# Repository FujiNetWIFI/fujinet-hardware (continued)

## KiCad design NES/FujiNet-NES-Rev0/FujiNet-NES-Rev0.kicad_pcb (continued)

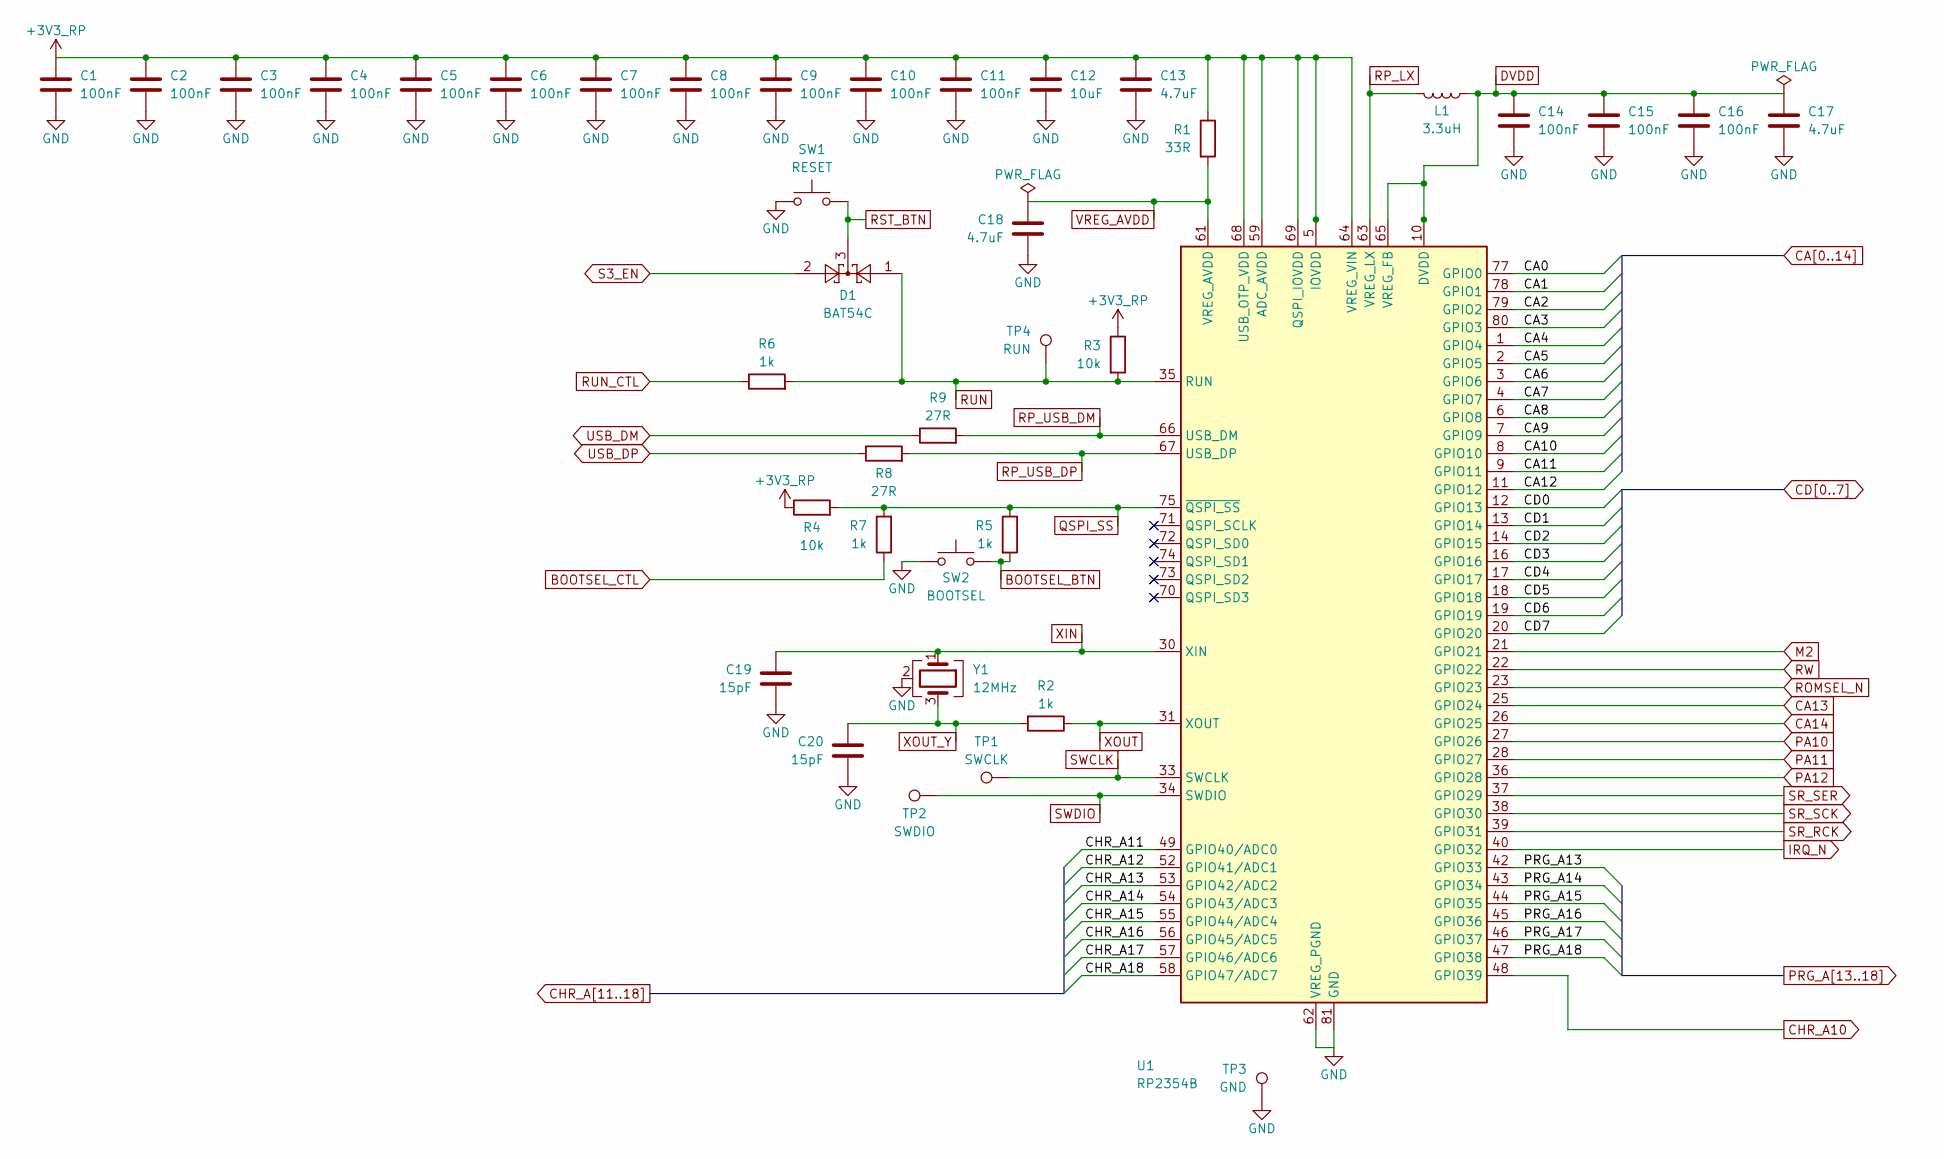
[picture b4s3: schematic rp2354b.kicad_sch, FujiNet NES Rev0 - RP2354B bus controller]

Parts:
C1, C2, C3, C4, C5, C6, C7, C8, C9, C10, C11, C14, C15, C16: 100nF; C_0603_1608Metric; MPN CC0603KRX7R9BB104; LCSC C14663
C12: 10uF; C_0603_1608Metric; MPN CL10A106KP8NNNC; LCSC C19702
C13, C17, C18: 4.7uF; C_0603_1608Metric; MPN CL10A475KO8NNNC; LCSC C19666
C19, C20: 15pF; C_0603_1608Metric; MPN CL10C150JB8NNNC; LCSC C1644
D1: BAT54C; SOT-23; MPN BAT54C,215; LCSC C37704
L1: 3.3uH; RPI_L_AOTA-B201610S3R3; MPN AOTA-B201610S3R3-101-T; LCSC C42411119
R1: 33R; R_0603_1608Metric; MPN 0603WAF330JT5E; LCSC C23140
R2, R5, R6, R7: 1k; R_0603_1608Metric; MPN 0603WAF1001T5E; LCSC C21190
R3, R4: 10k; R_0603_1608Metric; MPN 0603WAF1002T5E; LCSC C25804
R8, R9: 27R; R_0603_1608Metric; MPN 0603WAF270JT5E; LCSC C25190
SW1: RESET; SW_SPST_TL3342; MPN TL3342F160QG; LCSC C2886898
SW2: BOOTSEL; SW_SPST_TL3342; MPN TL3342F160QG; LCSC C2886898
TP1: SWCLK; TestPoint_Pad_D1.5mm
TP2: SWDIO; TestPoint_Pad_D1.5mm
TP3: GND; TestPoint_Pad_D1.5mm
TP4: RUN; TestPoint_Pad_D1.5mm
U1: RP2354B; QFN-80-1EP_10x10mm_P0.4mm_EP3.4x3.4mm; MPN RP2354B; LCSC C39843328
Y1: 12MHz; Crystal_SMD_3225-4Pin_3.2x2.5mm; MPN ABM8-272-T3; LCSC C20625731

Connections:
+3V3_RP: C1.1, C2.1, C3.1, C4.1, C5.1, C6.1, C7.1, C8.1, C9.1, C10.1, C11.1, C12.1, C13.1, R1.1, R3.1, R4.1, U1.5 (IOVDD), U1.15 (IOVDD), U1.24 (IOVDD), U1.29 (IOVDD), U1.41 (IOVDD), U1.50 (IOVDD), U1.59 (ADC_AVDD), U1.60 (IOVDD), U1.64 (VREG_VIN), U1.68 (USB_OTP_VDD), U1.69 (QSPI_IOVDD), U1.76 (IOVDD); also elsewhere on the board
BOOTSEL_BTN: R5.2, SW2.1
BOOTSEL_CTL: R7.1; also elsewhere on the board
CA0: U1.77 (GPIO0); also elsewhere on the board
CA1: U1.78 (GPIO1); also elsewhere on the board
CA2: U1.79 (GPIO2); also elsewhere on the board
CA3: U1.80 (GPIO3); also elsewhere on the board
CA4: U1.1 (GPIO4); also elsewhere on the board
CA5: U1.2 (GPIO5); also elsewhere on the board
CA6: U1.3 (GPIO6); also elsewhere on the board
CA7: U1.4 (GPIO7); also elsewhere on the board
CA8: U1.6 (GPIO8); also elsewhere on the board
CA9: U1.7 (GPIO9); also elsewhere on the board
CA10: U1.8 (GPIO10); also elsewhere on the board
CA11: U1.9 (GPIO11); also elsewhere on the board
CA12: U1.11 (GPIO12); also elsewhere on the board
CA13: U1.25 (GPIO24); also elsewhere on the board
CA14: U1.26 (GPIO25); also elsewhere on the board
CD0: U1.12 (GPIO13); also elsewhere on the board
CD1: U1.13 (GPIO14); also elsewhere on the board
CD2: U1.14 (GPIO15); also elsewhere on the board
CD3: U1.16 (GPIO16); also elsewhere on the board
CD4: U1.17 (GPIO17); also elsewhere on the board
CD5: U1.18 (GPIO18); also elsewhere on the board
CD6: U1.19 (GPIO19); also elsewhere on the board
CD7: U1.20 (GPIO20); also elsewhere on the board
CHR_A10: U1.48 (GPIO39); also elsewhere on the board
CHR_A11: U1.49 (GPIO40/ADC0); also elsewhere on the board
CHR_A12: U1.52 (GPIO41/ADC1); also elsewhere on the board
CHR_A13: U1.53 (GPIO42/ADC2); also elsewhere on the board
CHR_A14: U1.54 (GPIO43/ADC3); also elsewhere on the board
CHR_A15: U1.55 (GPIO44/ADC4); also elsewhere on the board
CHR_A16: U1.56 (GPIO45/ADC5); also elsewhere on the board
CHR_A17: U1.57 (GPIO46/ADC6); also elsewhere on the board
CHR_A18: U1.58 (GPIO47/ADC7); also elsewhere on the board
DVDD: C14.1, C15.1, C16.1, C17.1, L1.1, U1.10 (DVDD), U1.32 (DVDD), U1.51 (DVDD), U1.65 (VREG_FB)
GND: C1.2, C2.2, C3.2, C4.2, C5.2, C6.2, C7.2, C8.2, C9.2, C10.2, C11.2, C12.2, C13.2, C14.2, C15.2, C16.2, C17.2, C18.2, C19.2, C20.2, SW1.2, SW2.2, TP3.1, U1.62 (VREG_PGND), U1.81 (GND), Y1.2 (G), Y1.4 (G); also elsewhere on the board
IRQ_N: U1.40 (GPIO32); also elsewhere on the board
M2: U1.21 (GPIO21); also elsewhere on the board
PA10: U1.27 (GPIO26); also elsewhere on the board
PA11: U1.28 (GPIO27); also elsewhere on the board
PA12: U1.36 (GPIO28); also elsewhere on the board
PRG_A13: U1.42 (GPIO33); also elsewhere on the board
PRG_A14: U1.43 (GPIO34); also elsewhere on the board
PRG_A15: U1.44 (GPIO35); also elsewhere on the board
PRG_A16: U1.45 (GPIO36); also elsewhere on the board
PRG_A17: U1.46 (GPIO37); also elsewhere on the board
PRG_A18: U1.47 (GPIO38); also elsewhere on the board
QSPI_SS: R4.2, R5.1, R7.2, U1.75 (~QSPI_SS)
ROMSEL_N: U1.23 (GPIO23); also elsewhere on the board
RP_LX: L1.2, U1.63 (VREG_LX)
RP_USB_DM: R9.2, U1.66 (USB_DM)
RP_USB_DP: R8.2, U1.67 (USB_DP)
RST_BTN: D1.3, SW1.1
RUN: D1.1, R3.2, R6.2, TP4.1, U1.35 (RUN)
RUN_CTL: R6.1; also elsewhere on the board
RW: U1.22 (GPIO22); also elsewhere on the board
S3_EN: D1.2; also elsewhere on the board
SR_RCK: U1.39 (GPIO31); also elsewhere on the board
SR_SCK: U1.38 (GPIO30); also elsewhere on the board
SR_SER: U1.37 (GPIO29); also elsewhere on the board
SWCLK: TP1.1, U1.33 (SWCLK)
SWDIO: TP2.1, U1.34 (SWDIO)
USB_DM: R9.1; also elsewhere on the board
USB_DP: R8.1; also elsewhere on the board
VREG_AVDD: C18.1, R1.2, U1.61 (VREG_AVDD)
XIN: C19.1, U1.30 (XIN), Y1.1
XOUT: R2.1, U1.31 (XOUT)
XOUT_Y: C20.1, R2.2, Y1.3

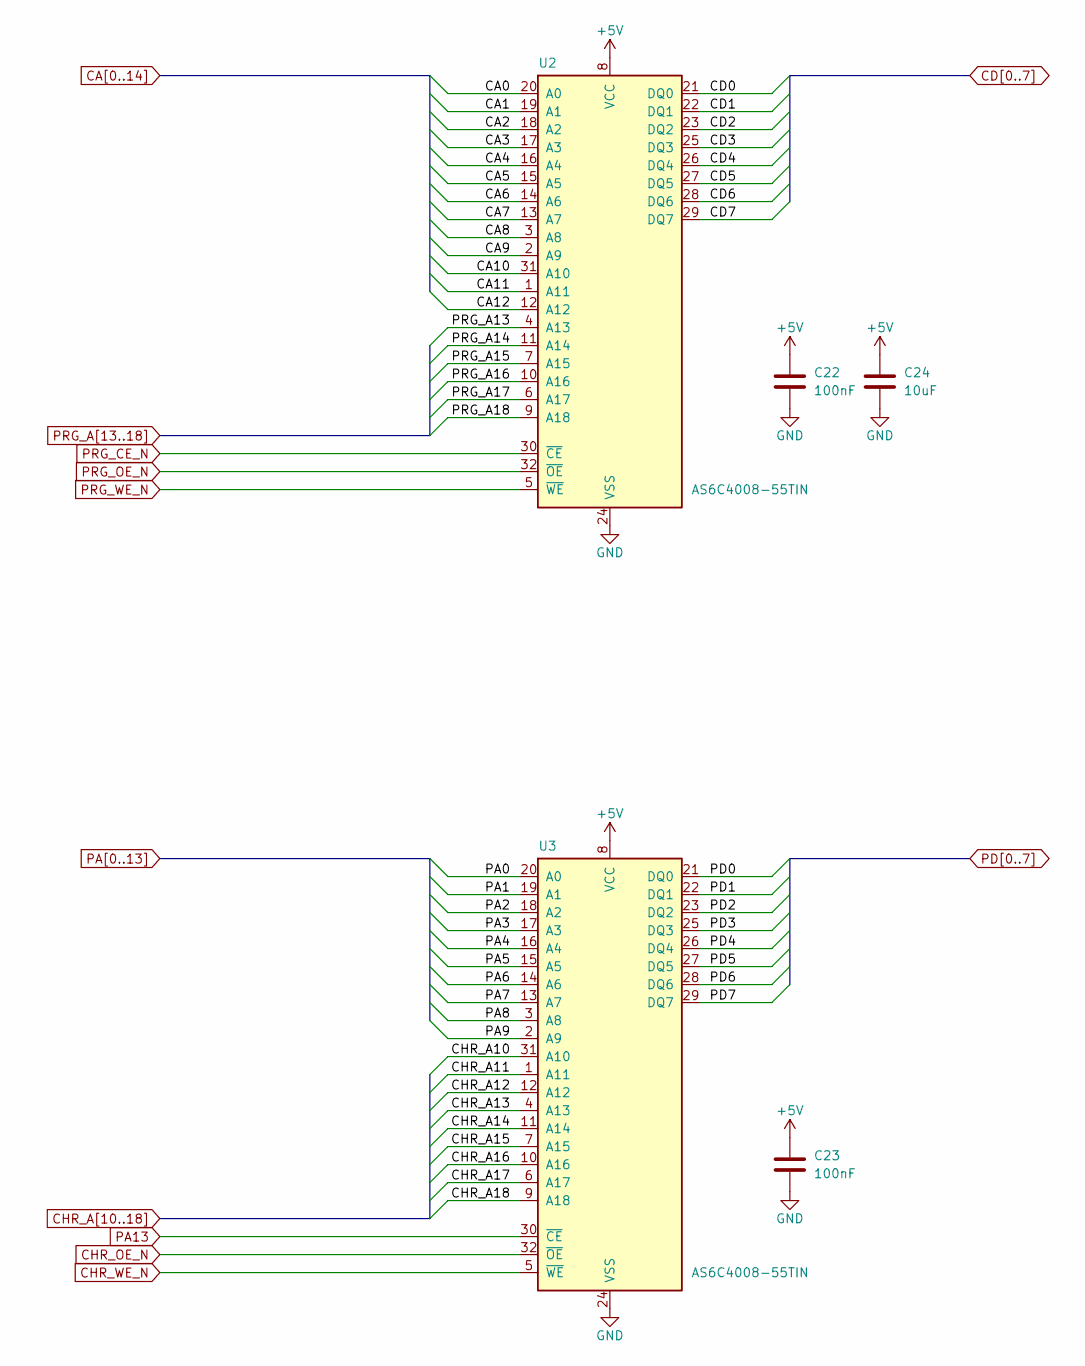
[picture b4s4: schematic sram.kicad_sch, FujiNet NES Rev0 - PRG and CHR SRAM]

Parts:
C22, C23: 100nF; C_0603_1608Metric; MPN CC0603KRX7R9BB104; LCSC C14663
C24: 10uF; C_0603_1608Metric; MPN CL10A106KP8NNNC; LCSC C19702
U2, U3: AS6C4008-55TIN; TSOP-I-32_18.4x8mm_P0.5mm; MPN AS6C4008-55TIN; LCSC C5569980

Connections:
+5V: C22.1, C23.1, C24.1, U2.8 (VCC), U3.8 (VCC); also elsewhere on the board
CA0: U2.20 (A0); also elsewhere on the board
CA1: U2.19 (A1); also elsewhere on the board
CA2: U2.18 (A2); also elsewhere on the board
CA3: U2.17 (A3); also elsewhere on the board
CA4: U2.16 (A4); also elsewhere on the board
CA5: U2.15 (A5); also elsewhere on the board
CA6: U2.14 (A6); also elsewhere on the board
CA7: U2.13 (A7); also elsewhere on the board
CA8: U2.3 (A8); also elsewhere on the board
CA9: U2.2 (A9); also elsewhere on the board
CA10: U2.31 (A10); also elsewhere on the board
CA11: U2.1 (A11); also elsewhere on the board
CA12: U2.12 (A12); also elsewhere on the board
CD0: U2.21 (DQ0); also elsewhere on the board
CD1: U2.22 (DQ1); also elsewhere on the board
CD2: U2.23 (DQ2); also elsewhere on the board
CD3: U2.25 (DQ3); also elsewhere on the board
CD4: U2.26 (DQ4); also elsewhere on the board
CD5: U2.27 (DQ5); also elsewhere on the board
CD6: U2.28 (DQ6); also elsewhere on the board
CD7: U2.29 (DQ7); also elsewhere on the board
CHR_A10: U3.31 (A10); also elsewhere on the board
CHR_A11: U3.1 (A11); also elsewhere on the board
CHR_A12: U3.12 (A12); also elsewhere on the board
CHR_A13: U3.4 (A13); also elsewhere on the board
CHR_A14: U3.11 (A14); also elsewhere on the board
CHR_A15: U3.7 (A15); also elsewhere on the board
CHR_A16: U3.10 (A16); also elsewhere on the board
CHR_A17: U3.6 (A17); also elsewhere on the board
CHR_A18: U3.9 (A18); also elsewhere on the board
CHR_OE_N: U3.32 (~OE); also elsewhere on the board
CHR_WE_N: U3.5 (~WE); also elsewhere on the board
GND: C22.2, C23.2, C24.2, U2.24 (VSS), U3.24 (VSS); also elsewhere on the board
PA0: U3.20 (A0); also elsewhere on the board
PA1: U3.19 (A1); also elsewhere on the board
PA2: U3.18 (A2); also elsewhere on the board
PA3: U3.17 (A3); also elsewhere on the board
PA4: U3.16 (A4); also elsewhere on the board
PA5: U3.15 (A5); also elsewhere on the board
PA6: U3.14 (A6); also elsewhere on the board
PA7: U3.13 (A7); also elsewhere on the board
PA8: U3.3 (A8); also elsewhere on the board
PA9: U3.2 (A9); also elsewhere on the board
PA13: U3.30 (~CE); also elsewhere on the board
PD0: U3.21 (DQ0); also elsewhere on the board
PD1: U3.22 (DQ1); also elsewhere on the board
PD2: U3.23 (DQ2); also elsewhere on the board
PD3: U3.25 (DQ3); also elsewhere on the board
PD4: U3.26 (DQ4); also elsewhere on the board
PD5: U3.27 (DQ5); also elsewhere on the board
PD6: U3.28 (DQ6); also elsewhere on the board
PD7: U3.29 (DQ7); also elsewhere on the board
PRG_A13: U2.4 (A13); also elsewhere on the board
PRG_A14: U2.11 (A14); also elsewhere on the board
PRG_A15: U2.7 (A15); also elsewhere on the board
PRG_A16: U2.10 (A16); also elsewhere on the board
PRG_A17: U2.6 (A17); also elsewhere on the board
PRG_A18: U2.9 (A18); also elsewhere on the board
PRG_CE_N: U2.30 (~CE); also elsewhere on the board
PRG_OE_N: U2.32 (~OE); also elsewhere on the board
PRG_WE_N: U2.5 (~WE); also elsewhere on the board

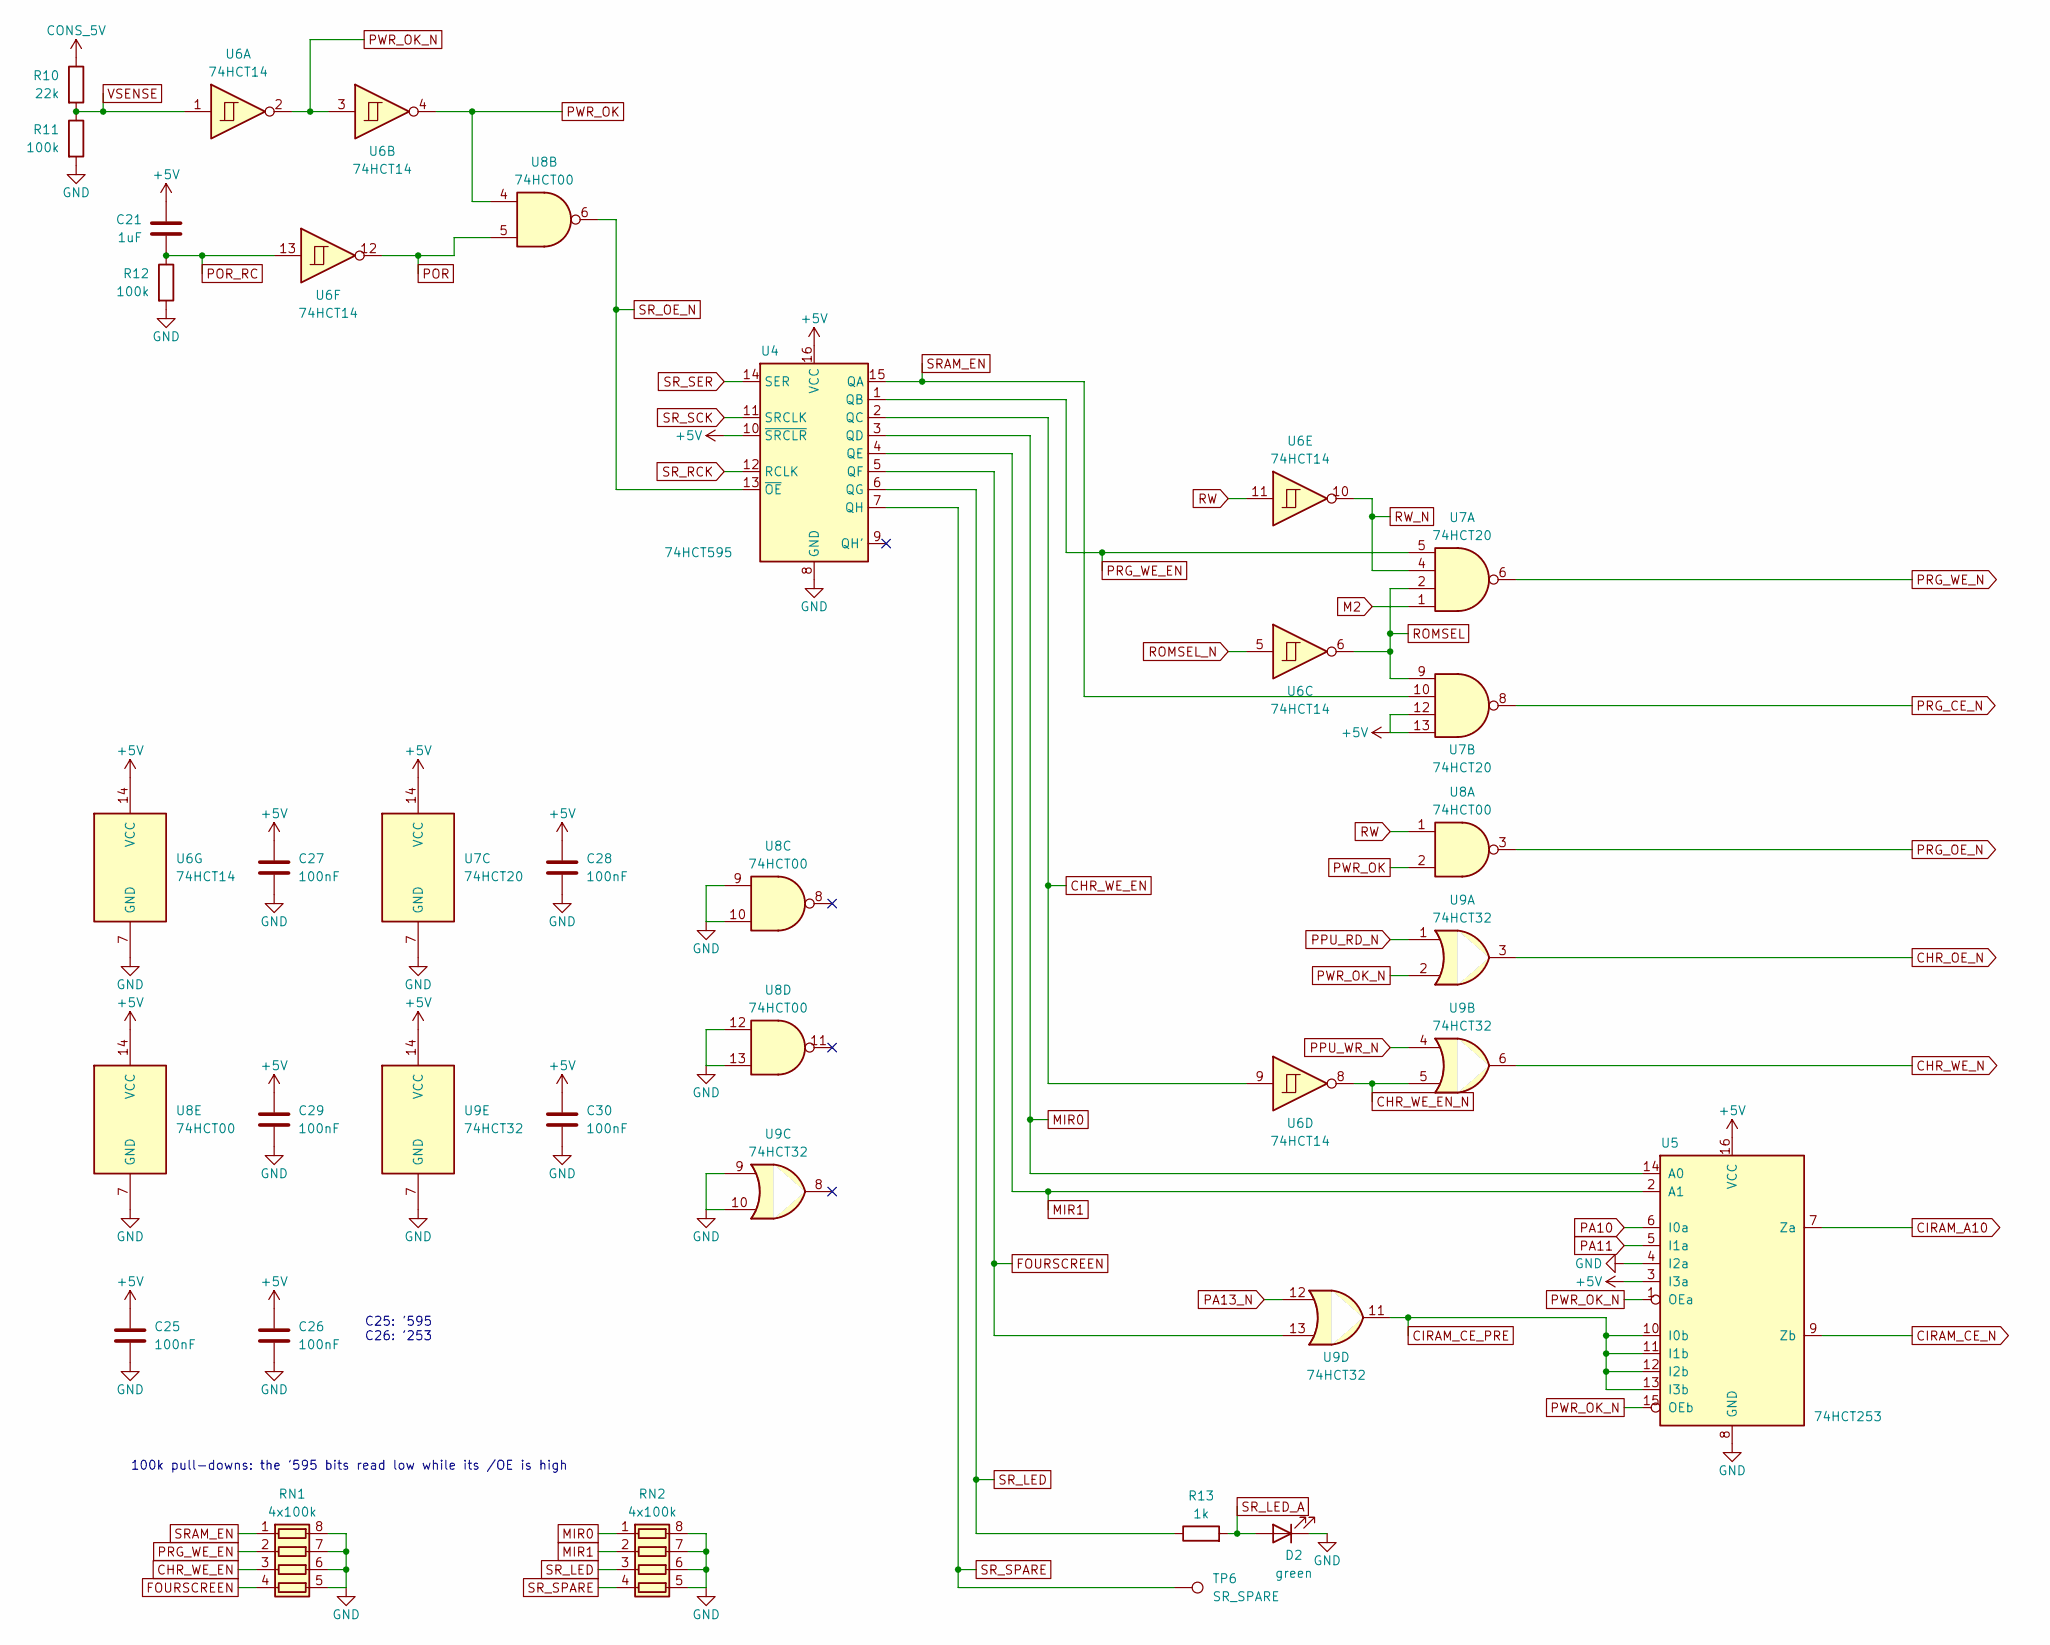
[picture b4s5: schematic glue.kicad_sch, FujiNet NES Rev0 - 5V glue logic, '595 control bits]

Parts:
C21: 1uF; C_0603_1608Metric; MPN CL10A105KB8NNNC; LCSC C15849
C25, C26, C27, C28, C29, C30: 100nF; C_0603_1608Metric; MPN CC0603KRX7R9BB104; LCSC C14663
D2: green; LED_0603_1608Metric; MPN KT-0603G; LCSC C12624
R10: 22k; R_0603_1608Metric; MPN 0603WAF2202T5E; LCSC C31850
R11, R12: 100k; R_0603_1608Metric; MPN 0603WAF1003T5E; LCSC C25803
R13: 1k; R_0603_1608Metric; MPN 0603WAF1001T5E; LCSC C21190
RN1, RN2: 4x100k; R_Array_Convex_4x0603; MPN 4D03WGJ0104T5E; LCSC C1996
TP6: SR_SPARE; TestPoint_Pad_D1.5mm
U4: 74HCT595; SOIC-16_3.9x9.9mm_P1.27mm; MPN 74HCT595D,118; LCSC C282339
U5: 74HCT253; SOIC-16_3.9x9.9mm_P1.27mm; MPN 74HCT253D,653; LCSC C547509
U6: 74HCT14; SOIC-14_3.9x8.7mm_P1.27mm; MPN SN74HCT14DR; LCSC C6769
U7: 74HCT20; SOIC-14_3.9x8.7mm_P1.27mm; MPN CD74HCT20M96; LCSC C2878717
U8: 74HCT00; SOIC-14_3.9x8.7mm_P1.27mm; MPN SN74HCT00DR; LCSC C6764
U9: 74HCT32; SOIC-14_3.9x8.7mm_P1.27mm; MPN 74HCT32D,653; LCSC C5985

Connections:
+5V: C21.2, C25.1, C26.1, C27.1, C28.1, C29.1, C30.1, U4.10 (~SRCLR), U4.16 (VCC), U5.3 (I3a), U5.16 (VCC), U6.14 (VCC), U7.12, U7.13, U7.14 (VCC), U8.14 (VCC), U9.14 (VCC); also elsewhere on the board
CHR_OE_N: U9.3; also elsewhere on the board
CHR_WE_EN: RN1.3 (R3.1), U4.2 (QC), U6.9
CHR_WE_EN_N: U6.8, U9.5
CHR_WE_N: U9.6; also elsewhere on the board
CIRAM_A10: U5.7 (Za); also elsewhere on the board
CIRAM_CE_N: U5.9 (Zb); also elsewhere on the board
CIRAM_CE_PRE: U5.10 (I0b), U5.11 (I1b), U5.12 (I2b), U5.13 (I3b), U9.11
CONS_5V: R10.1; also elsewhere on the board
FOURSCREEN: RN1.4 (R4.1), U4.5 (QF), U9.13
GND: C25.2, C26.2, C27.2, C28.2, C29.2, C30.2, D2.1 (K), R11.2, R12.2, RN1.5 (R4.2), RN1.6 (R3.2), RN1.7 (R2.2), RN1.8 (R1.2), RN2.5 (R4.2), RN2.6 (R3.2), RN2.7 (R2.2), RN2.8 (R1.2), U4.8 (GND), U5.4 (I2a), U5.8 (GND), U6.7 (GND), U7.7 (GND), U8.7 (GND), U8.9, U8.10, U8.12, U8.13, U9.7 (GND), U9.9, U9.10; also elsewhere on the board
M2: U7.1; also elsewhere on the board
MIR0: RN2.1 (R1.1), U4.3 (QD), U5.14 (A0)
MIR1: RN2.2 (R2.1), U4.4 (QE), U5.2 (A1)
PA10: U5.6 (I0a); also elsewhere on the board
PA11: U5.5 (I1a); also elsewhere on the board
PA13_N: U9.12; also elsewhere on the board
POR: U6.12, U8.5
POR_RC: C21.1, R12.1, U6.13
PPU_RD_N: U9.1; also elsewhere on the board
PPU_WR_N: U9.4; also elsewhere on the board
PRG_CE_N: U7.8; also elsewhere on the board
PRG_OE_N: U8.3; also elsewhere on the board
PRG_WE_EN: RN1.2 (R2.1), U4.1 (QB), U7.5
PRG_WE_N: U7.6; also elsewhere on the board
PWR_OK: U6.4, U8.2, U8.4
PWR_OK_N: U5.1 (OEa), U5.15 (OEb), U6.2, U6.3, U9.2
ROMSEL: U6.6, U7.2, U7.9
ROMSEL_N: U6.5; also elsewhere on the board
RW: U6.11, U8.1; also elsewhere on the board
RW_N: U6.10, U7.4
SRAM_EN: RN1.1 (R1.1), U4.15 (QA), U7.10
SR_LED: R13.1, RN2.3 (R3.1), U4.6 (QG)
SR_LED_A: D2.2 (A), R13.2
SR_OE_N: U4.13 (~OE), U8.6
SR_RCK: U4.12 (RCLK); also elsewhere on the board
SR_SCK: U4.11 (SRCLK); also elsewhere on the board
SR_SER: U4.14 (SER); also elsewhere on the board
SR_SPARE: RN2.4 (R4.1), TP6.1, U4.7 (QH)
VSENSE: R10.2, R11.1, U6.1

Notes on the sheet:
C25: '595 C26: '253
100k pull-downs: the '595 bits read low while its /OE is high

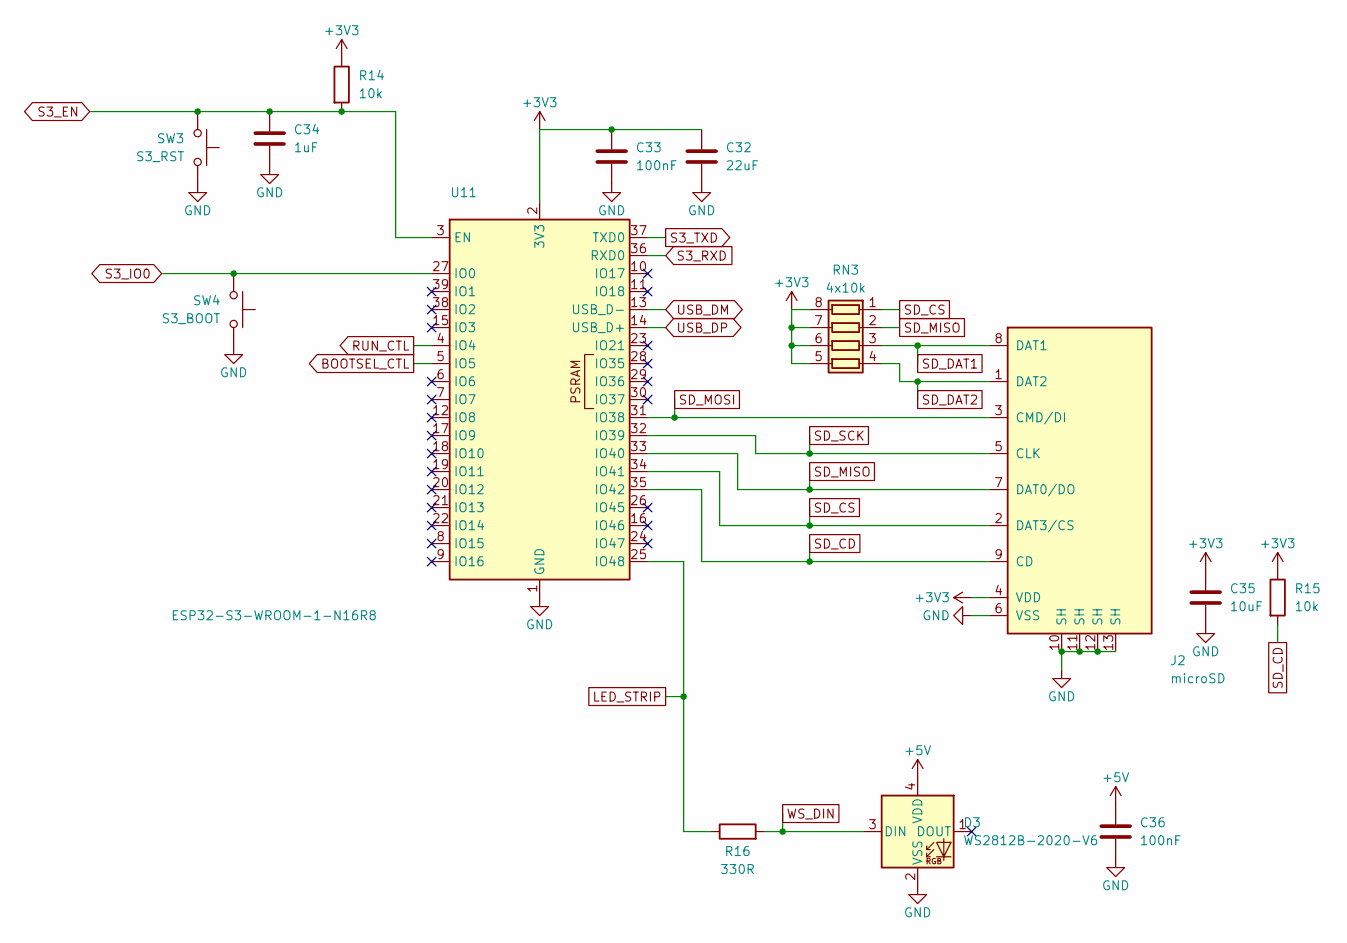
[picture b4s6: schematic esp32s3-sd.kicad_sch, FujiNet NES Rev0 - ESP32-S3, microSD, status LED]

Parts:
C32: 22uF; C_0805_2012Metric; MPN CL21A226MAQNNNE; LCSC C45783
C33, C36: 100nF; C_0603_1608Metric; MPN CC0603KRX7R9BB104; LCSC C14663
C34: 1uF; C_0603_1608Metric; MPN CL10A105KB8NNNC; LCSC C15849
C35: 10uF; C_0603_1608Metric; MPN CL10A106KP8NNNC; LCSC C19702
D3: WS2812B-2020-V6; LED_WS2812B-2020_PLCC4_2.0x2.0mm; MPN WS2812B-2020-V6; LCSC C52917434
J2: microSD; TF-SMD_TF-015; MPN TF-015; LCSC C113206
R14, R15: 10k; R_0603_1608Metric; MPN 0603WAF1002T5E; LCSC C25804
R16: 330R; R_0603_1608Metric; MPN 0603WAF3300T5E; LCSC C23138
RN3: 4x10k; R_Array_Convex_4x0603; MPN 4D03WGJ0103T5E; LCSC C29718
SW3: S3_RST; SW_SPST_TL3342; MPN TL3342F160QG; LCSC C2886898
SW4: S3_BOOT; SW_SPST_TL3342; MPN TL3342F160QG; LCSC C2886898
U11: ESP32-S3-WROOM-1-N16R8; ESP32-S3-WROOM-1; MPN ESP32-S3-WROOM-1-N16R8; LCSC C2913202

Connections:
+3V3: C32.1, C33.1, C35.1, J2.4 (VDD), R14.1, R15.1, RN3.5 (R4.2), RN3.6 (R3.2), RN3.7 (R2.2), RN3.8 (R1.2), U11.2 (3V3); also elsewhere on the board
+5V: C36.1, D3.4 (VDD); also elsewhere on the board
BOOTSEL_CTL: U11.5 (IO5); also elsewhere on the board
GND: C32.2, C33.2, C34.2, C35.2, C36.2, D3.2 (VSS), J2.6 (VSS), J2.10 (SH), J2.11 (SH), J2.12 (SH), J2.13 (SH), SW3.2, SW4.2, U11.1 (GND), U11.40 (GND), U11.41 (GND); also elsewhere on the board
LED_STRIP: R16.1, U11.25 (IO48)
RUN_CTL: U11.4 (IO4); also elsewhere on the board
S3_EN: C34.1, R14.2, SW3.1, U11.3 (EN); also elsewhere on the board
S3_IO0: SW4.1, U11.27 (IO0); also elsewhere on the board
S3_RXD: U11.36 (RXD0); also elsewhere on the board
S3_TXD: U11.37 (TXD0); also elsewhere on the board
SD_CD: J2.9 (CD), R15.2, U11.35 (IO42)
SD_CS: J2.2 (DAT3/CS), RN3.1 (R1.1), U11.34 (IO41)
SD_DAT1: J2.8 (DAT1), RN3.3 (R3.1)
SD_DAT2: J2.1 (DAT2), RN3.4 (R4.1)
SD_MISO: J2.7 (DAT0/DO), RN3.2 (R2.1), U11.33 (IO40)
SD_MOSI: J2.3 (CMD/DI), U11.31 (IO38)
SD_SCK: J2.5 (CLK), U11.32 (IO39)
USB_DM: U11.13 (USB_D-); also elsewhere on the board
USB_DP: U11.14 (USB_D+); also elsewhere on the board
WS_DIN: D3.3 (DIN), R16.2

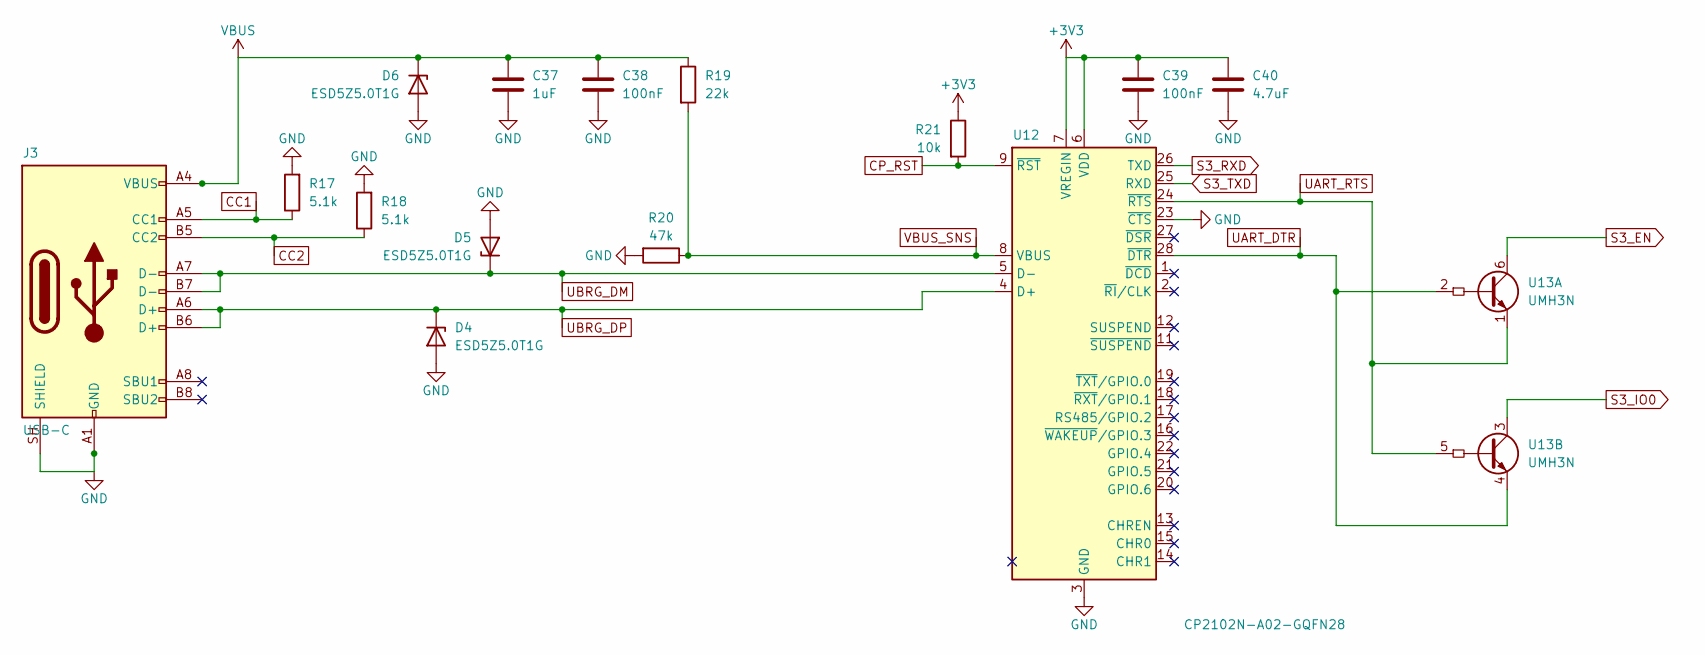
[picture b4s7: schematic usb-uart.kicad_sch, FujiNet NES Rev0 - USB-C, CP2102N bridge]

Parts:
C37: 1uF; C_0603_1608Metric; MPN CL10A105KB8NNNC; LCSC C15849
C38, C39: 100nF; C_0603_1608Metric; MPN CC0603KRX7R9BB104; LCSC C14663
C40: 4.7uF; C_0603_1608Metric; MPN CL10A475KO8NNNC; LCSC C19666
D4, D5, D6: ESD5Z5.0T1G; D_SOD-523; MPN ESD5Z5.0T1G; LCSC C82044
J3: USB-C; USB_C_Receptacle_HRO_TYPE-C-31-M-12; MPN TYPE-C-31-M-12; LCSC C165948
R17, R18: 5.1k; R_0603_1608Metric; MPN 0603WAF5101T5E; LCSC C23186
R19: 22k; R_0603_1608Metric; MPN 0603WAF2202T5E; LCSC C31850
R20: 47k; R_0603_1608Metric; MPN 0603WAF4702T5E; LCSC C25819
R21: 10k; R_0603_1608Metric; MPN 0603WAF1002T5E; LCSC C25804
U12: CP2102N-A02-GQFN28; QFN-28-1EP_5x5mm_P0.5mm_EP3.35x3.35mm; MPN CP2102N-A02-GQFN28R; LCSC C964632
U13: UMH3N; SOT-363_SC-70-6; MPN UMH3N; LCSC C62892

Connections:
+3V3: C39.1, C40.1, R21.1, U12.6 (VDD), U12.7 (VREGIN); also elsewhere on the board
CC1: J3.A5 (CC1), R17.1
CC2: J3.B5 (CC2), R18.1
CP_RST: R21.2, U12.9 (~RST)
GND: C37.2, C38.2, C39.2, C40.2, D4.2 (A), D5.2 (A), D6.2 (A), J3.A1 (GND), J3.A12 (GND), J3.B1 (GND), J3.B12 (GND), J3.SH (SHIELD), R17.2, R18.2, R20.2, U12.3 (GND), U12.23 (~CTS), U12.29 (GND); also elsewhere on the board
S3_EN: U13.6 (C1); also elsewhere on the board
S3_IO0: U13.3 (C2); also elsewhere on the board
S3_RXD: U12.26 (TXD); also elsewhere on the board
S3_TXD: U12.25 (RXD); also elsewhere on the board
UART_DTR: U12.28 (~DTR), U13.2 (B1), U13.4 (E2)
UART_RTS: U12.24 (~RTS), U13.1 (E1), U13.5 (B2)
UBRG_DM: D5.1 (K), J3.A7 (D-), J3.B7 (D-), U12.5 (D-)
UBRG_DP: D4.1 (K), J3.A6 (D+), J3.B6 (D+), U12.4 (D+)
VBUS: C37.1, C38.1, D6.1 (K), J3.A4 (VBUS), J3.A9 (VBUS), J3.B4 (VBUS), J3.B9 (VBUS), R19.1; also elsewhere on the board
VBUS_SNS: R19.2, R20.1, U12.8 (VBUS)

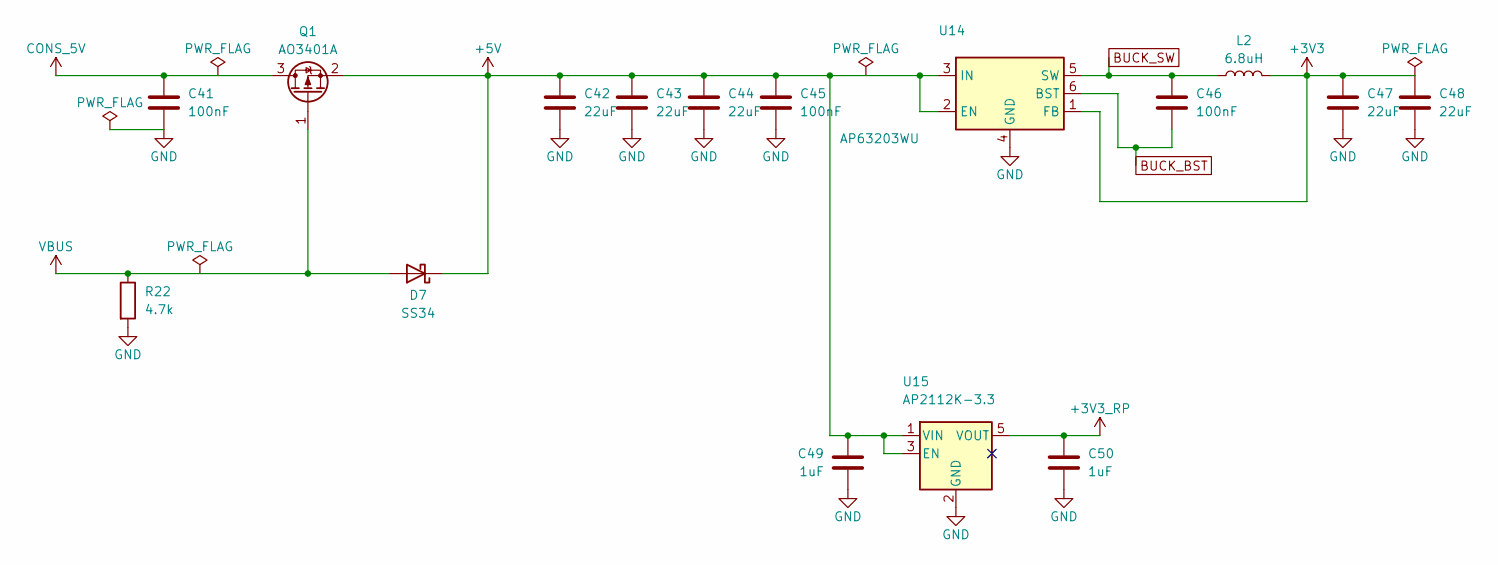
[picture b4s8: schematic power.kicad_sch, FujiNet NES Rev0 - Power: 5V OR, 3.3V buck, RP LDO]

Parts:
C41, C45, C46: 100nF; C_0603_1608Metric; MPN CC0603KRX7R9BB104; LCSC C14663
C42, C43, C44, C47, C48: 22uF; C_0805_2012Metric; MPN CL21A226MAQNNNE; LCSC C45783
C49, C50: 1uF; C_0603_1608Metric; MPN CL10A105KB8NNNC; LCSC C15849
D7: SS34; D_SMA; MPN SS34; LCSC C8678
L2: 6.8uH; L_Sunlord_SWPA4030S; MPN SWPA4030S6R8MT; LCSC C62684
Q1: AO3401A; SOT-23; MPN AO3401A; LCSC C15127
R22: 4.7k; R_0603_1608Metric; MPN 0603WAF4701T5E; LCSC C23162
U14: AP63203WU; TSOT-23-6; MPN AP63203WU-7; LCSC C780769
U15: AP2112K-3.3; SOT-23-5; MPN AP2112K-3.3TRG1; LCSC C51118

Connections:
+3V3: C47.1, C48.1, L2.2, U14.1 (FB); also elsewhere on the board
+3V3_RP: C50.1, U15.5 (VOUT); also elsewhere on the board
+5V: C42.1, C43.1, C44.1, C45.1, C49.1, D7.1 (K), Q1.2 (S), U14.2 (EN), U14.3 (IN), U15.1 (VIN), U15.3 (EN); also elsewhere on the board
BUCK_BST: C46.2, U14.6 (BST)
BUCK_SW: C46.1, L2.1, U14.5 (SW)
CONS_5V: C41.1, Q1.3 (D); also elsewhere on the board
GND: C41.2, C42.2, C43.2, C44.2, C45.2, C47.2, C48.2, C49.2, C50.2, R22.2, U14.4 (GND), U15.2 (GND); also elsewhere on the board
VBUS: D7.2 (A), Q1.1 (G), R22.1; also elsewhere on the board
